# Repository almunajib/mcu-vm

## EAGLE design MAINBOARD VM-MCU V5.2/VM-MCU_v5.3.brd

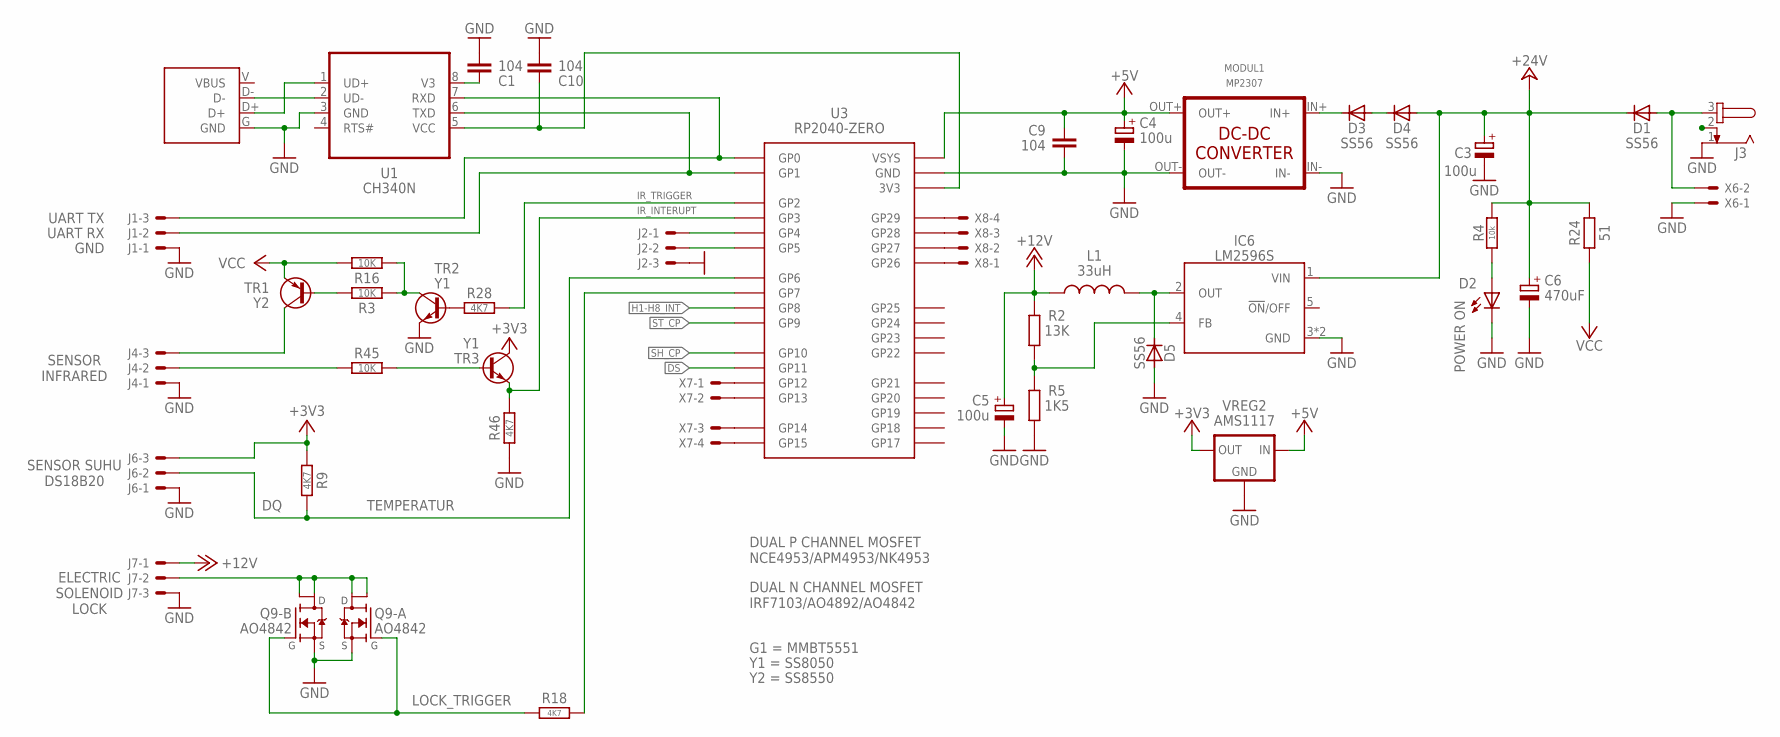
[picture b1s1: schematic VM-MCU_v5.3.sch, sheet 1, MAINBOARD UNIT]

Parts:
C1, C9, C10: 104; C1206
C3, C4, C5: 100u; UD-6,3X7,7_NICHICON
C6: 470uF; E5-10,5
D1, D3, D4, D5: SS56; DO214AC
D2: POWER ON; LED2835
IC6: LM2596S; TO263-5
J1, J6, J7: SOKET-3P_KF2510-2.54; KF2510-3P
J2: SOKET-3P_JST-XH-2.54; 3P-JST-XH
J3: JACK-DC_5.5X2.1MM; DC-5.5X2.1
J4: SOKET-3P_MOLEX-3.96; 3P-MOLEX
L1: 33uH; CDRH104
MODUL1: MP2307
Q9: AO4842; SO-8
R2: 13K; R1206
R3, R16, R45: 10K; R1206
R4: 10k; R1206
R5: 1K5; R1206
R9, R18, R28, R46: 4K7; R1206
R24: 51; R2512
TR1: Y2; SOT23-BEC
TR2, TR3: Y1; SOT23-BEC
U1: CH340N; SO-8
U3: RP2040-ZERO; PICO-ZERO
U$3: USB-C_BREAKOUT_; USB-C_4P
VREG2: AMS1117; SOT223
X6: SOKET-2P_MOLEX-3.96; 2P-MOLEX
X7, X8: SOKET-4P_JST-XH-2.54; 4P-JST-XH

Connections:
+3V3: J6.3, R9.1, TR3.C, VREG2.4 (OUT); also elsewhere on the board
+5V: C4.+, C9.1, MODUL1.OUT+, U3.5V (VSYS), VREG2.3 (IN); also elsewhere on the board
+12V: C5.+, J7.1, L1.1, R2.1
+24V: C3.+, C6.+, D1.C, D4.A, IC6.1 (VIN), R4.2, R24.2; also elsewhere on the board
DS: U3.P11 (GP11); also elsewhere on the board
GND: C1.2, C3.-, C4.-, C5.-, C6.-, C9.2, C10.2, D2.C, D5.A, IC6.3 (GND), IC6.6 (GND), J1.1, J2.3, J3.1, J4.1, J6.1, J7.3, MODUL1.IN-, MODUL1.OUT-, Q9.1 (S), Q9.3 (S), R5.2, R46.1, TR2.E, U1.3 (GND), U3.G (GND), U$3.G (GND), VREG2.1 (GND), X6.1; also elsewhere on the board
H1-H8_INT: U3.P8 (GP8); also elsewhere on the board
unnamed: J1.3, U1.7 (RXD), U3.P0 (GP0)
unnamed: J1.2, U1.6 (TXD), U3.P1 (GP1)
unnamed: D1.A, J3.3, X6.2
unnamed: D2.A, R4.1
unnamed: J2.1, U3.P4 (GP4)
unnamed: R3.2, R16.2, TR2.C
unnamed: R3.1, TR1.B
unnamed: J2.2, U3.P5 (GP5)
unnamed: C10.1, U1.5 (VCC), U3.3V3
unnamed: J4.3, TR1.C
unnamed: Q9.2 (G), Q9.4 (G), R18.2
unnamed: C1.1, U1.8 (V3)
unnamed: U1.2 (UD-), U$3.D-
unnamed: U1.1 (UD+), U$3.D+
unnamed: J7.2, Q9.5 (D1), Q9.6 (D2), Q9.7 (D2), Q9.8 (D1)
unnamed: D3.C, MODUL1.IN+
unnamed: D3.A, D4.C
unnamed: U3.P12 (GP12), X7.1
unnamed: U3.P13 (GP13), X7.2
unnamed: U3.P14 (GP14), X7.3
unnamed: U3.P15 (GP15), X7.4
unnamed: D5.C, IC6.2 (OUT), L1.2
unnamed: U3.P26 (GP26), X8.1
unnamed: U3.P27 (GP27), X8.2
unnamed: IC6.4 (FB), R2.2, R5.1
unnamed: U3.P28 (GP28), X8.3
unnamed: R28.1, TR2.B
unnamed: R45.1, TR3.B
unnamed: U3.P29 (GP29), X8.4
unnamed: J4.2, R45.2
P2: R28.2, U3.P2 (GP2)
P3: R46.2, TR3.E, U3.P3 (GP3)
P6: J6.2, R9.2, U3.P6 (GP6)
P7: R18.1, U3.P7 (GP7)
SH_CP: U3.P10 (GP10); also elsewhere on the board
ST_CP: U3.P9 (GP9); also elsewhere on the board
VCC: R16.1, R24.1, TR1.E

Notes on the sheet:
UART RX
UART TX
SENSOR SUHU DS18B20
SENSOR INFRARED
ELECTRIC SOLENOID LOCK
IR_TRIGGER
TEMPERATUR
IR_INTERUPT
DUAL P CHANNEL MOSFET NCE4953/APM4953/NK4953
DUAL N CHANNEL MOSFET IRF7103/AO4892/AO4842
LOCK_TRIGGER
G1 = MMBT5551
GND
Y1 = SS8050
Y2 = SS8550

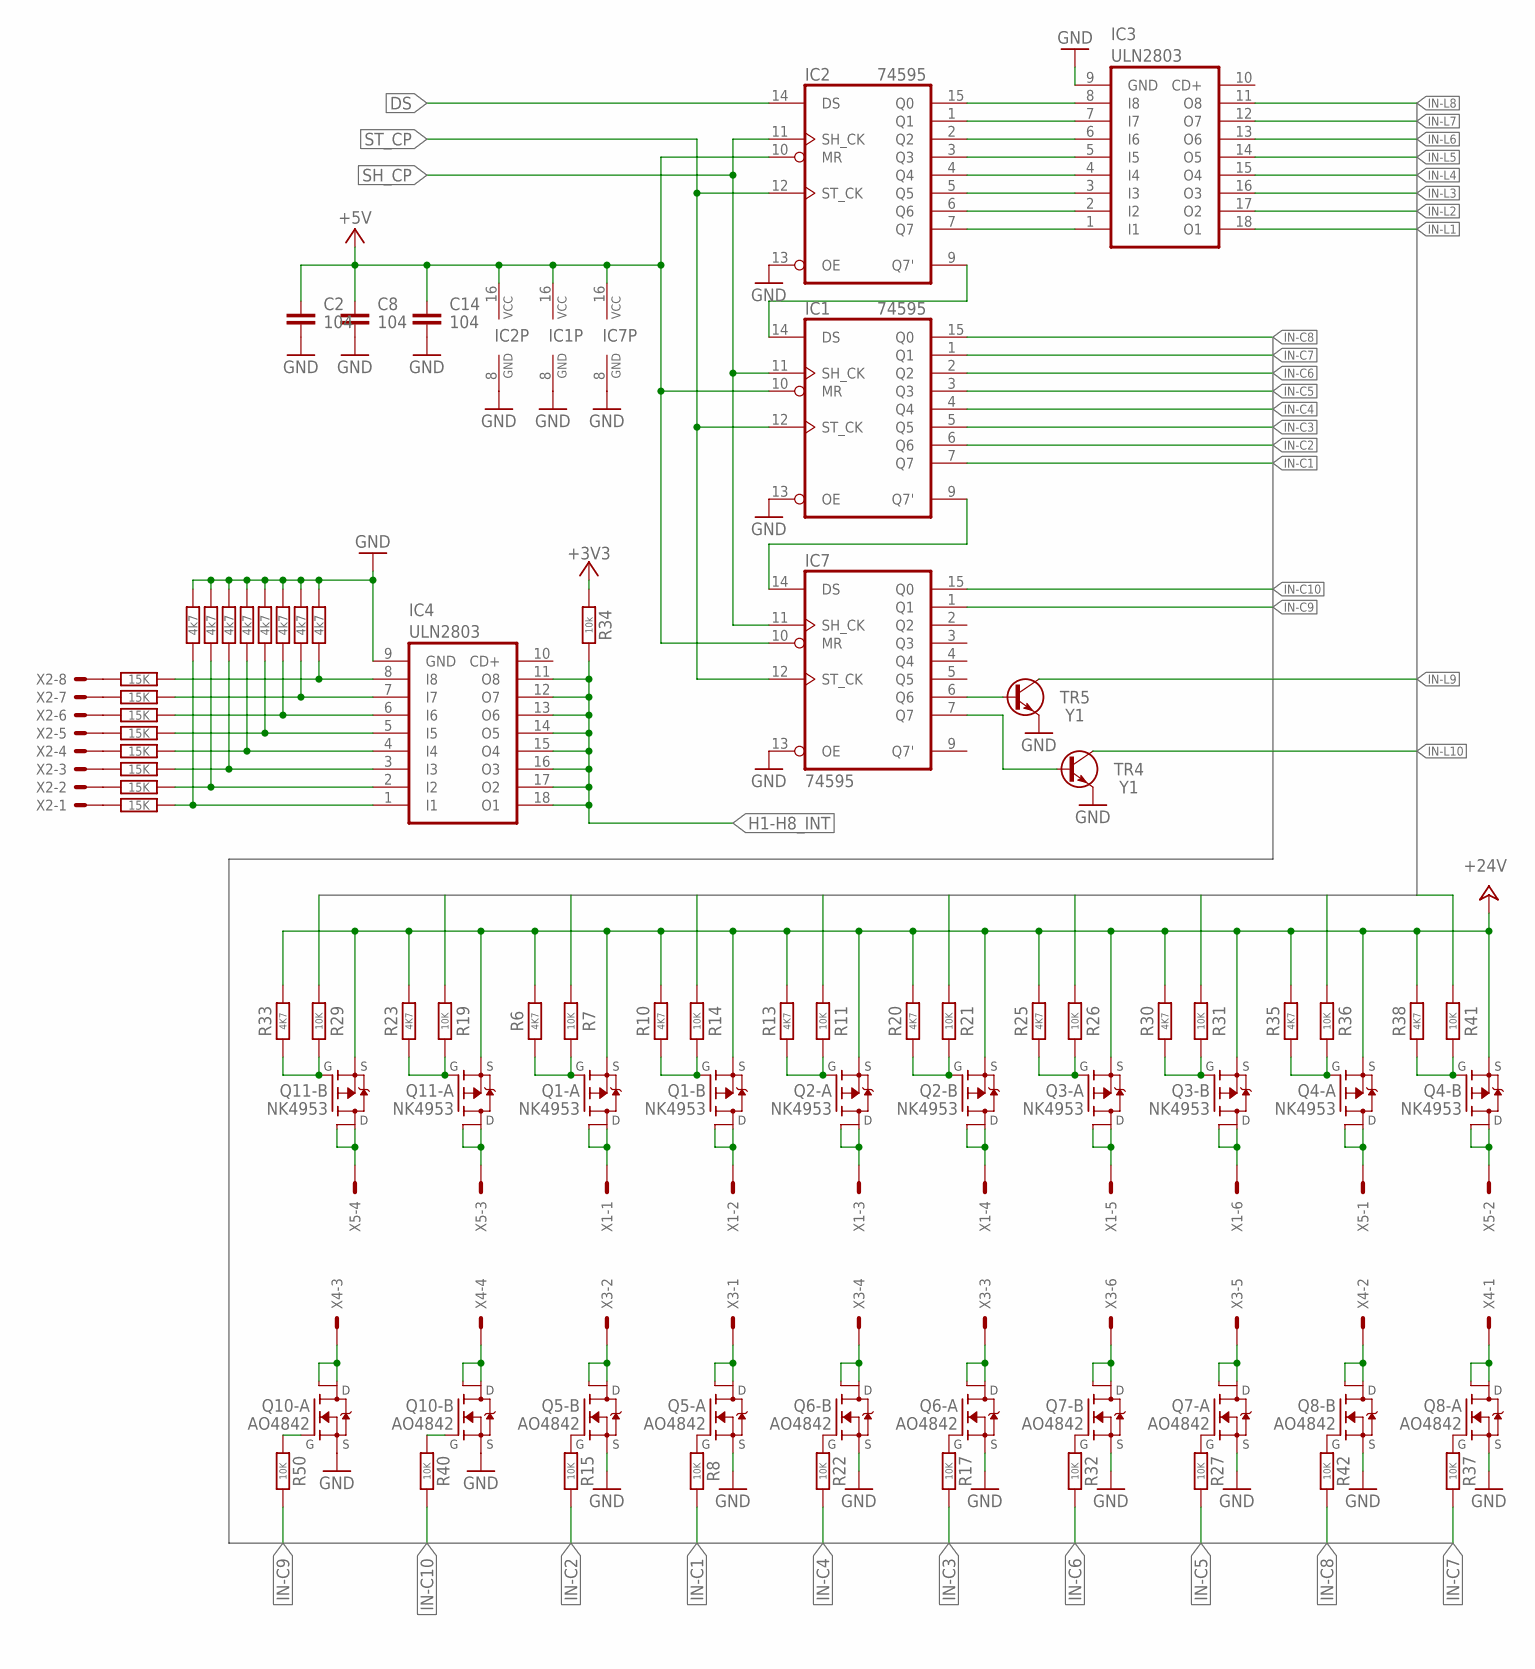
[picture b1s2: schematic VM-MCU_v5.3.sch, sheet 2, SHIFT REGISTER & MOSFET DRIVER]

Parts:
C2, C8, C14: 104; C1206
IC1, IC2, IC7: 74595; SO16
IC3, IC4: ULN2803; SO18W
Q1, Q2, Q3, Q4, Q11: NK4953; SO-8
Q5, Q6, Q7, Q8, Q10: AO4842; SO-8
R1, R12, R39, R43, R44, R47, R48, R49: 15K; R0805
R6, R10, R13, R20, R23, R25, R30, R33, R35, R38: 4K7; R1206
R7, R8, R11, R14, R15, R17, R19, R21, R22, R26, R27, R29, R31, R32, R36, R37, R40, R41, R42, R50: 10K; R1206
R34: 10k; R1206
R51, R52, R53, R54, R55, R56, R57, R58: 4k7; R0805
TR4, TR5: Y1; SOT23-BEC
X1, X3: SOKET-6P_MOLEX-3.96; 6P-MOLEX
X2: SOKET-8P_MOLEX-3.96; 8P-MOLEX
X4, X5: SOKET-4P_MOLEX-3.96; 4P-MOLEX

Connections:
+3V3: R34.2; also elsewhere on the board
+5V: C2.1, C8.1, C14.1, IC1.10 (MR), IC1.16 (VCC), IC2.10 (MR), IC2.16 (VCC), IC7.10 (MR), IC7.16 (VCC); also elsewhere on the board
+24V: Q1.1 (S), Q1.3 (S), Q2.1 (S), Q2.3 (S), Q3.1 (S), Q3.3 (S), Q4.1 (S), Q4.3 (S), Q11.1 (S), Q11.3 (S), R6.1, R10.1, R13.1, R20.1, R23.1, R25.1, R30.1, R33.1, R35.1, R38.1; also elsewhere on the board
C1: Q5.5 (D1), Q5.6 (D2), X3.2
C2: Q5.7 (D2), Q5.8 (D1), X3.1
C3: Q6.5 (D1), Q6.6 (D2), X3.4
C4: Q6.7 (D2), Q6.8 (D1), X3.3
C5: Q7.5 (D1), Q7.6 (D2), X3.6
C6: Q7.7 (D2), Q7.8 (D1), X3.5
C7: Q8.5 (D1), Q8.6 (D2), X4.2
C8: Q8.7 (D2), Q8.8 (D1), X4.1
DS: IC2.14 (DS); also elsewhere on the board
GND: C2.2, C8.2, C14.2, IC1.8 (GND), IC1.13 (OE), IC2.8 (GND), IC2.13 (OE), IC3.9 (GND), IC4.9 (GND), IC7.8 (GND), IC7.13 (OE), Q5.1 (S), Q5.3 (S), Q6.1 (S), Q6.3 (S), Q7.1 (S), Q7.3 (S), Q8.1 (S), Q8.3 (S), Q10.1 (S), Q10.3 (S), R51.1, R52.1, R53.1, R54.1, R55.1, R56.1, R57.1, R58.1, TR4.E, TR5.E; also elsewhere on the board
H1-H8_INT: IC4.11 (O8), IC4.12 (O7), IC4.13 (O6), IC4.14 (O5), IC4.15 (O4), IC4.16 (O3), IC4.17 (O2), IC4.18 (O1), R34.1; also elsewhere on the board
I1: IC4.6 (I6), R39.1, R53.2
I2: IC4.5 (I5), R43.1, R54.2
I3: IC4.4 (I4), R44.1, R55.2
I4: IC4.3 (I3), R47.1, R56.2
I5: IC4.2 (I2), R48.1, R57.2
I6: IC4.1 (I1), R49.1, R58.2
IN-C1: IC1.7 (Q7), R8.2
IN-C2: IC1.6 (Q6), R15.2
IN-C3: IC1.5 (Q5), R17.2
IN-C4: IC1.4 (Q4), R22.2
IN-C5: IC1.3 (Q3), R27.2
IN-C6: IC1.2 (Q2), R32.2
IN-C7: IC1.1 (Q1), R37.2
IN-C8: IC1.15 (Q0), R42.2
IN-C9: IC7.1 (Q1), R50.2
IN-C10: IC7.15 (Q0), R40.2
IN-L1: IC3.18 (O1), R7.2
IN-L2: IC3.17 (O2), R14.2
IN-L3: IC3.16 (O3), R11.2
IN-L4: IC3.15 (O4), R21.2
IN-L5: IC3.14 (O5), R26.2
IN-L6: IC3.13 (O6), R31.2
IN-L7: IC3.12 (O7), R36.2
IN-L8: IC3.11 (O8), R41.2
IN-L9: R19.2, TR5.C
IN-L10: R29.2, TR4.C
L1: Q1.7 (D2), Q1.8 (D1), X1.1
L2: Q1.5 (D1), Q1.6 (D2), X1.2
L3: Q2.7 (D2), Q2.8 (D1), X1.3
L4: Q2.5 (D1), Q2.6 (D2), X1.4
L5: Q3.7 (D2), Q3.8 (D1), X1.5
L6: Q3.5 (D1), Q3.6 (D2), X1.6
L7: Q4.7 (D2), Q4.8 (D1), X5.1
L8: Q4.5 (D1), Q4.6 (D2), X5.2
unnamed: IC4.8 (I8), R12.1, R51.2
unnamed: IC4.7 (I7), R1.1, R52.2
unnamed: IC2.15 (Q0), IC3.8 (I8)
unnamed: R43.2, X2.5
unnamed: R44.2, X2.4
unnamed: IC2.1 (Q1), IC3.7 (I7)
unnamed: Q1.2 (G), R6.2, R7.1
unnamed: R47.2, X2.3
unnamed: Q5.2 (G), R8.1
unnamed: Q5.4 (G), R15.1
unnamed: Q1.4 (G), R10.2, R14.1
unnamed: IC2.2 (Q2), IC3.6 (I6)
unnamed: Q2.2 (G), R11.1, R13.2
unnamed: R39.2, X2.6
unnamed: R48.2, X2.2
unnamed: IC2.3 (Q3), IC3.5 (I5)
unnamed: Q6.2 (G), R17.1
unnamed: R1.2, X2.7
unnamed: IC2.4 (Q4), IC3.4 (I4)
unnamed: R49.2, X2.1
unnamed: Q6.4 (G), R22.1
unnamed: Q2.4 (G), R20.2, R21.1
unnamed: Q7.2 (G), R27.1
unnamed: IC2.5 (Q5), IC3.3 (I3)
unnamed: IC2.6 (Q6), IC3.2 (I2)
unnamed: IC2.7 (Q7), IC3.1 (I1)
unnamed: Q7.4 (G), R32.1
unnamed: Q8.2 (G), R37.1
unnamed: Q3.2 (G), R25.2, R26.1
unnamed: Q8.4 (G), R42.1
unnamed: R12.2, X2.8
unnamed: IC1.9 (Q7'), IC7.14 (DS)
unnamed: Q10.4 (G), R40.1
unnamed: Q3.4 (G), R30.2, R31.1
unnamed: Q11.4 (G), R29.1, R33.2
unnamed: Q10.2 (G), R50.1
unnamed: Q11.2 (G), R19.1, R23.2
unnamed: IC7.7 (Q7), TR4.B
unnamed: IC7.6 (Q6), TR5.B
unnamed: Q11.7 (D2), Q11.8 (D1), X5.3
unnamed: Q4.2 (G), R35.2, R36.1
unnamed: Q11.5 (D1), Q11.6 (D2), X5.4
unnamed: Q10.7 (D2), Q10.8 (D1), X4.3
unnamed: Q10.5 (D1), Q10.6 (D2), X4.4
unnamed: Q4.4 (G), R38.2, R41.1
unnamed: IC1.14 (DS), IC2.9 (Q7')
SH_CP: IC1.11 (SH_CK), IC2.11 (SH_CK), IC7.11 (SH_CK); also elsewhere on the board
ST_CP: IC1.12 (ST_CK), IC2.12 (ST_CK), IC7.12 (ST_CK); also elsewhere on the board

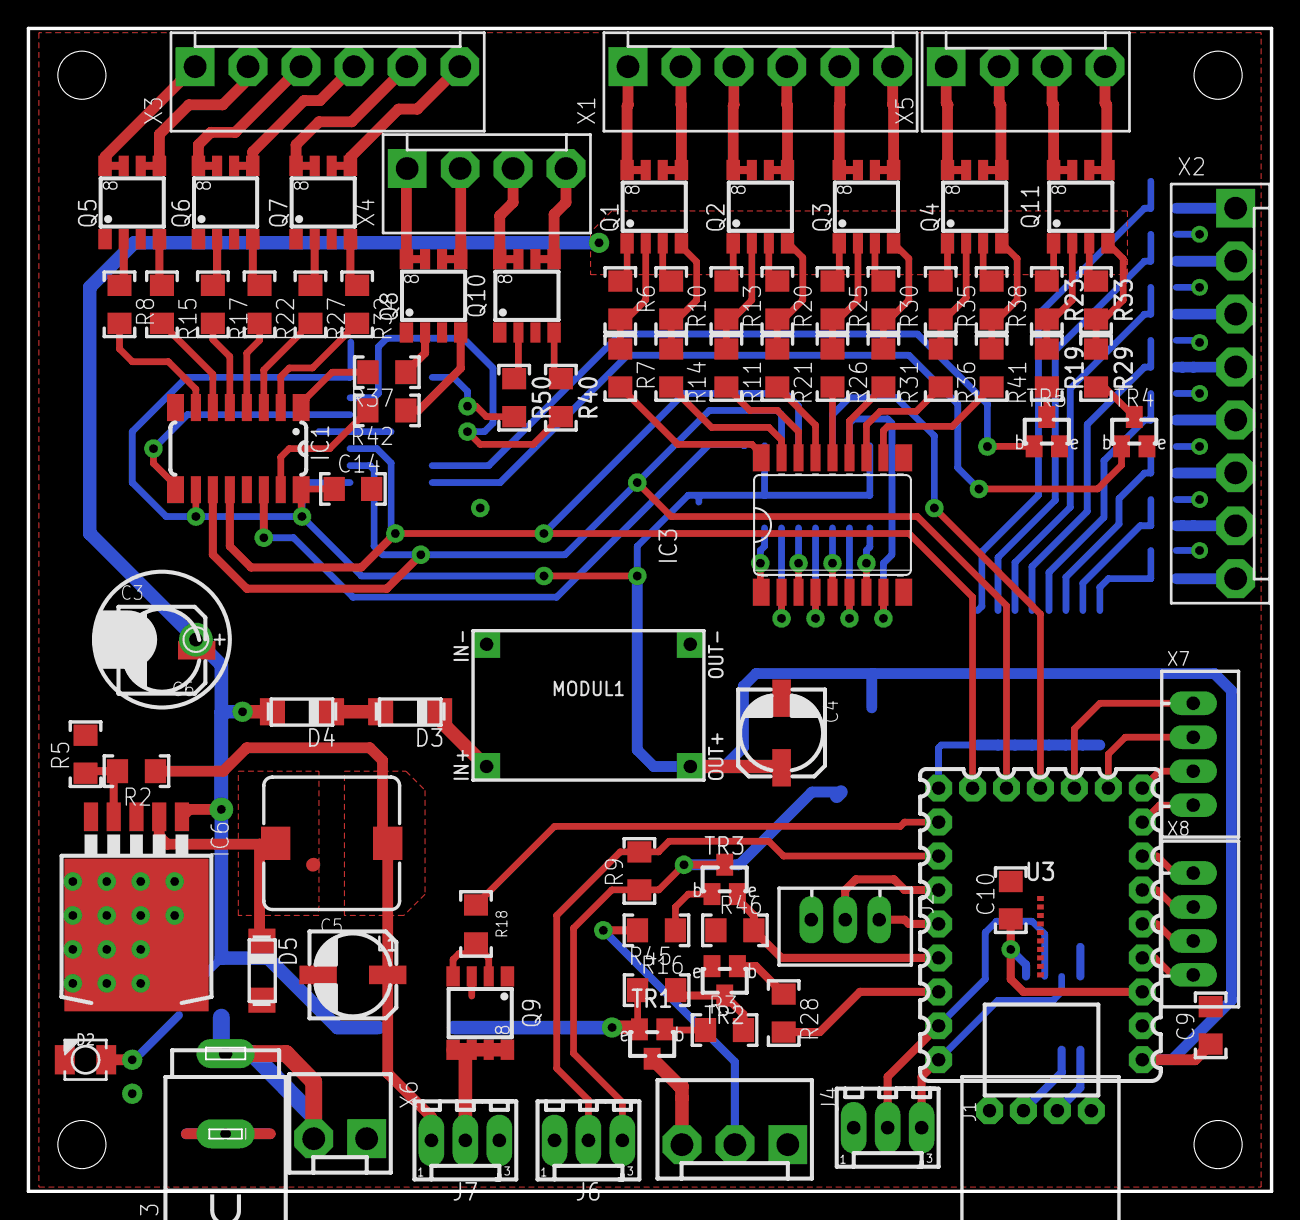
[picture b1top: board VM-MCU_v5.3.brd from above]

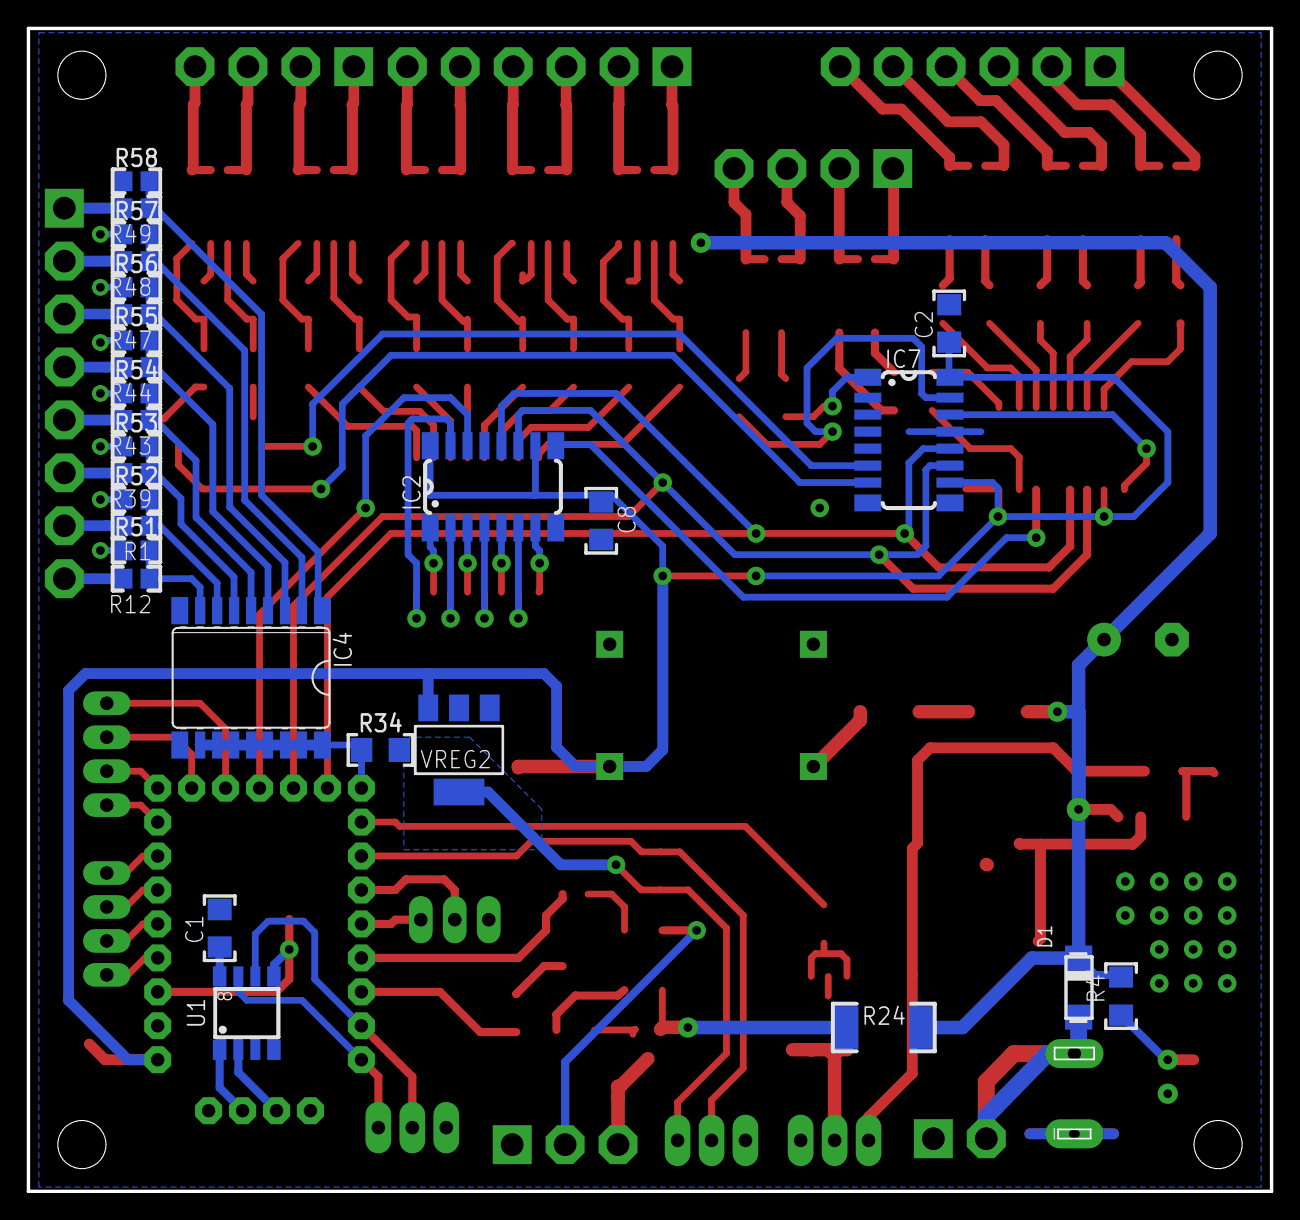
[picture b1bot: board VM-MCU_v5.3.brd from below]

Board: 2 copper layers, 93.0 x 87.0 mm, 116 parts (28 on the bottom side), 132 nets.

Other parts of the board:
U$1: BOX-PLC_115X90_V2

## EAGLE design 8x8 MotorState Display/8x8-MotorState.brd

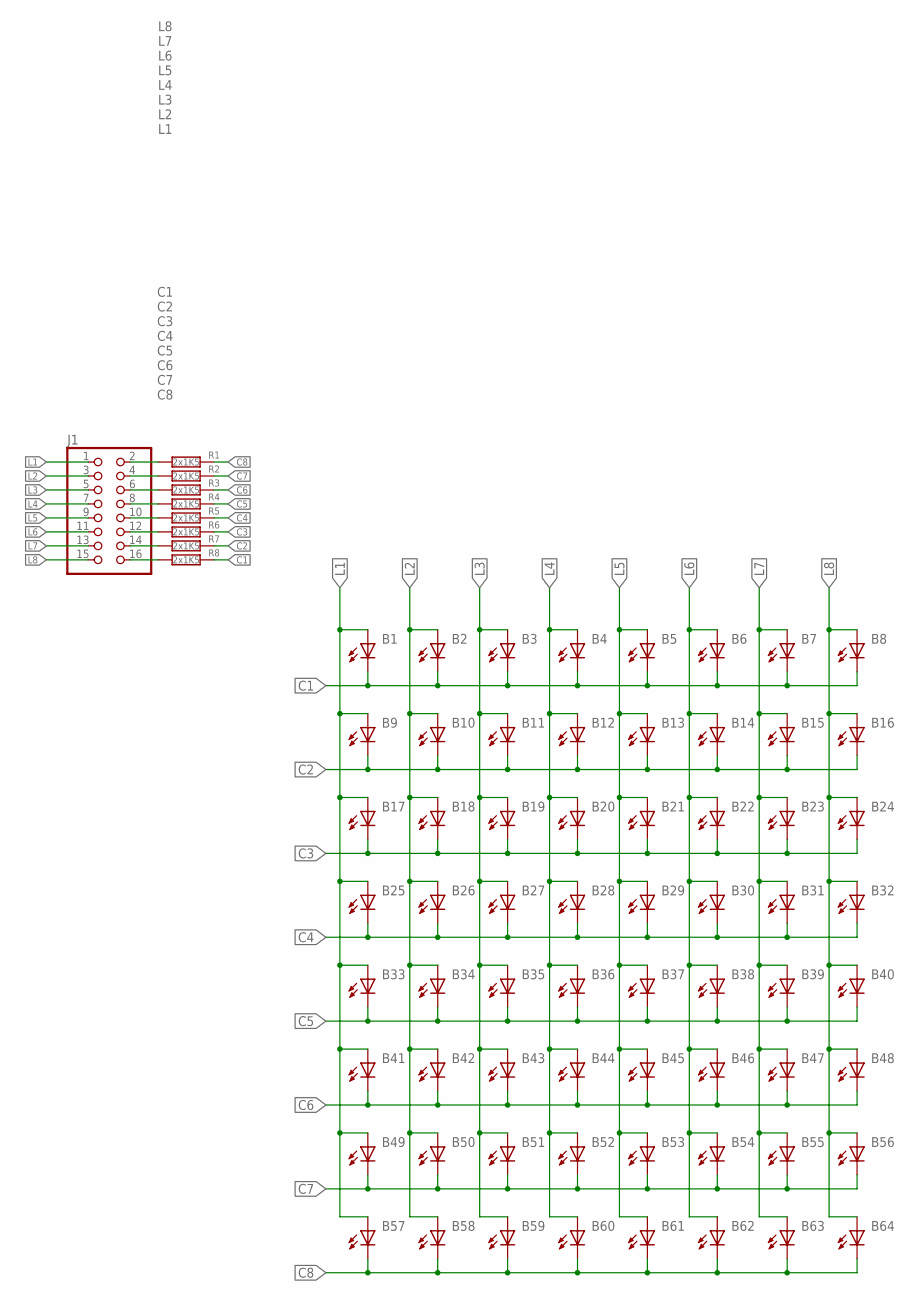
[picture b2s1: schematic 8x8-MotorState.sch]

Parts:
B1, B2, B3, B4, B5, B6, B7, B8, B9, B10, B11, B12, B13, B14, B15, B16, B17, B18, B19, B20, B21, B22, B23, B24, B25, B26, B27, B28, B29, B30, B31, B32, B33, B34, B35, B36, B37, B38, B39, B40, B41, B42, B43, B44, B45, B46, B47, B48, B49, B50, B51, B52, B53, B54, B55, B56, B57, B58, B59, B60, B61, B62, B63, B64: LED2835
J1: PINHEAD_2X8PTH; PINHEAD-2X08
R1, R2, R3, R4, R5, R6, R7, R8: 2x1K5; R1206

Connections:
C1: B1.C, B2.C, B3.C, B4.C, B5.C, B6.C, B7.C, B8.C, R8.1
C2: B9.C, B10.C, B11.C, B12.C, B13.C, B14.C, B15.C, B16.C, R7.1
C3: B17.C, B18.C, B19.C, B20.C, B21.C, B22.C, B23.C, B24.C, R6.1
C4: B25.C, B26.C, B27.C, B28.C, B29.C, B30.C, B31.C, B32.C, R5.1
C5: B33.C, B34.C, B35.C, B36.C, B37.C, B38.C, B39.C, B40.C, R4.1
C6: B41.C, B42.C, B43.C, B44.C, B45.C, B46.C, B47.C, B48.C, R3.1
C7: B49.C, B50.C, B51.C, B52.C, B53.C, B54.C, B55.C, B56.C, R2.1
C8: B57.C, B58.C, B59.C, B60.C, B61.C, B62.C, B63.C, B64.C, R1.1
L1: B1.A, B9.A, B17.A, B25.A, B33.A, B41.A, B49.A, B57.A, J1.1
L2: B2.A, B10.A, B18.A, B26.A, B34.A, B42.A, B50.A, B58.A, J1.3
L3: B3.A, B11.A, B19.A, B27.A, B35.A, B43.A, B51.A, B59.A, J1.5
L4: B4.A, B12.A, B20.A, B28.A, B36.A, B44.A, B52.A, B60.A, J1.7
L5: B5.A, B13.A, B21.A, B29.A, B37.A, B45.A, B53.A, B61.A, J1.9
L6: B6.A, B14.A, B22.A, B30.A, B38.A, B46.A, B54.A, B62.A, J1.11
L7: B7.A, B15.A, B23.A, B31.A, B39.A, B47.A, B55.A, B63.A, J1.13
L8: B8.A, B16.A, B24.A, B32.A, B40.A, B48.A, B56.A, B64.A, J1.15
unnamed: J1.2, R1.2
unnamed: J1.4, R2.2
unnamed: J1.6, R3.2
unnamed: J1.8, R4.2
unnamed: J1.10, R5.2
unnamed: J1.12, R6.2
unnamed: J1.14, R7.2
unnamed: J1.16, R8.2

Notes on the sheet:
C1 C2 C3 C4 C5 C6 C7 C8
L8 L7 L6 L5 L4 L3 L2 L1

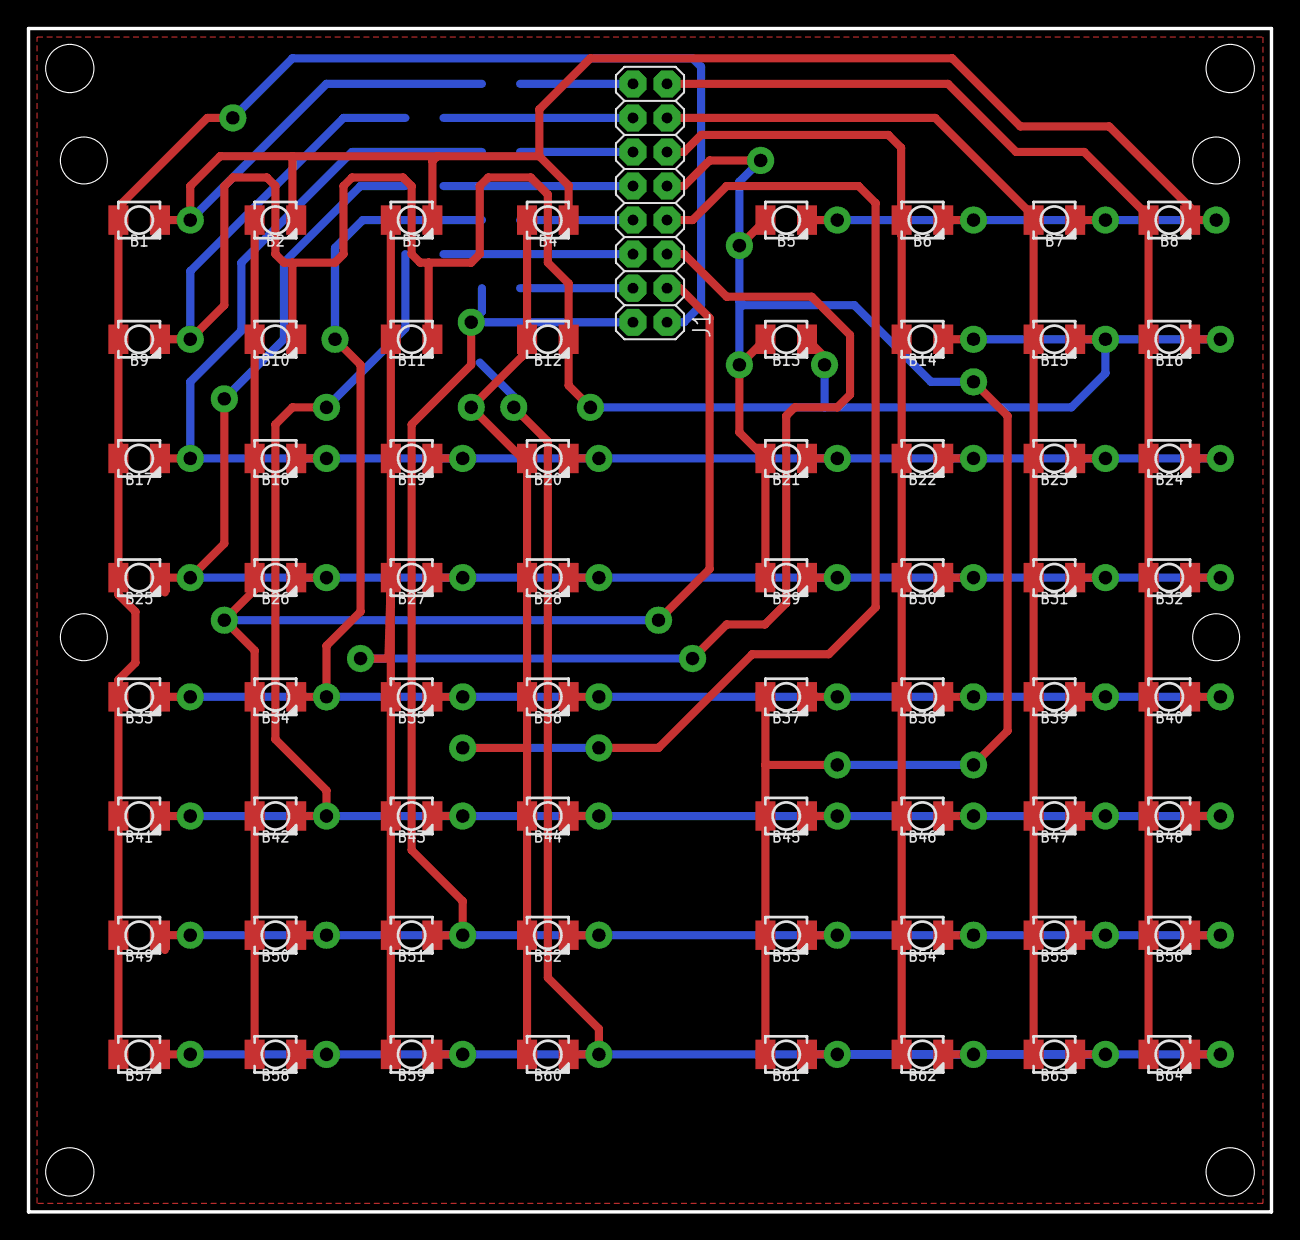
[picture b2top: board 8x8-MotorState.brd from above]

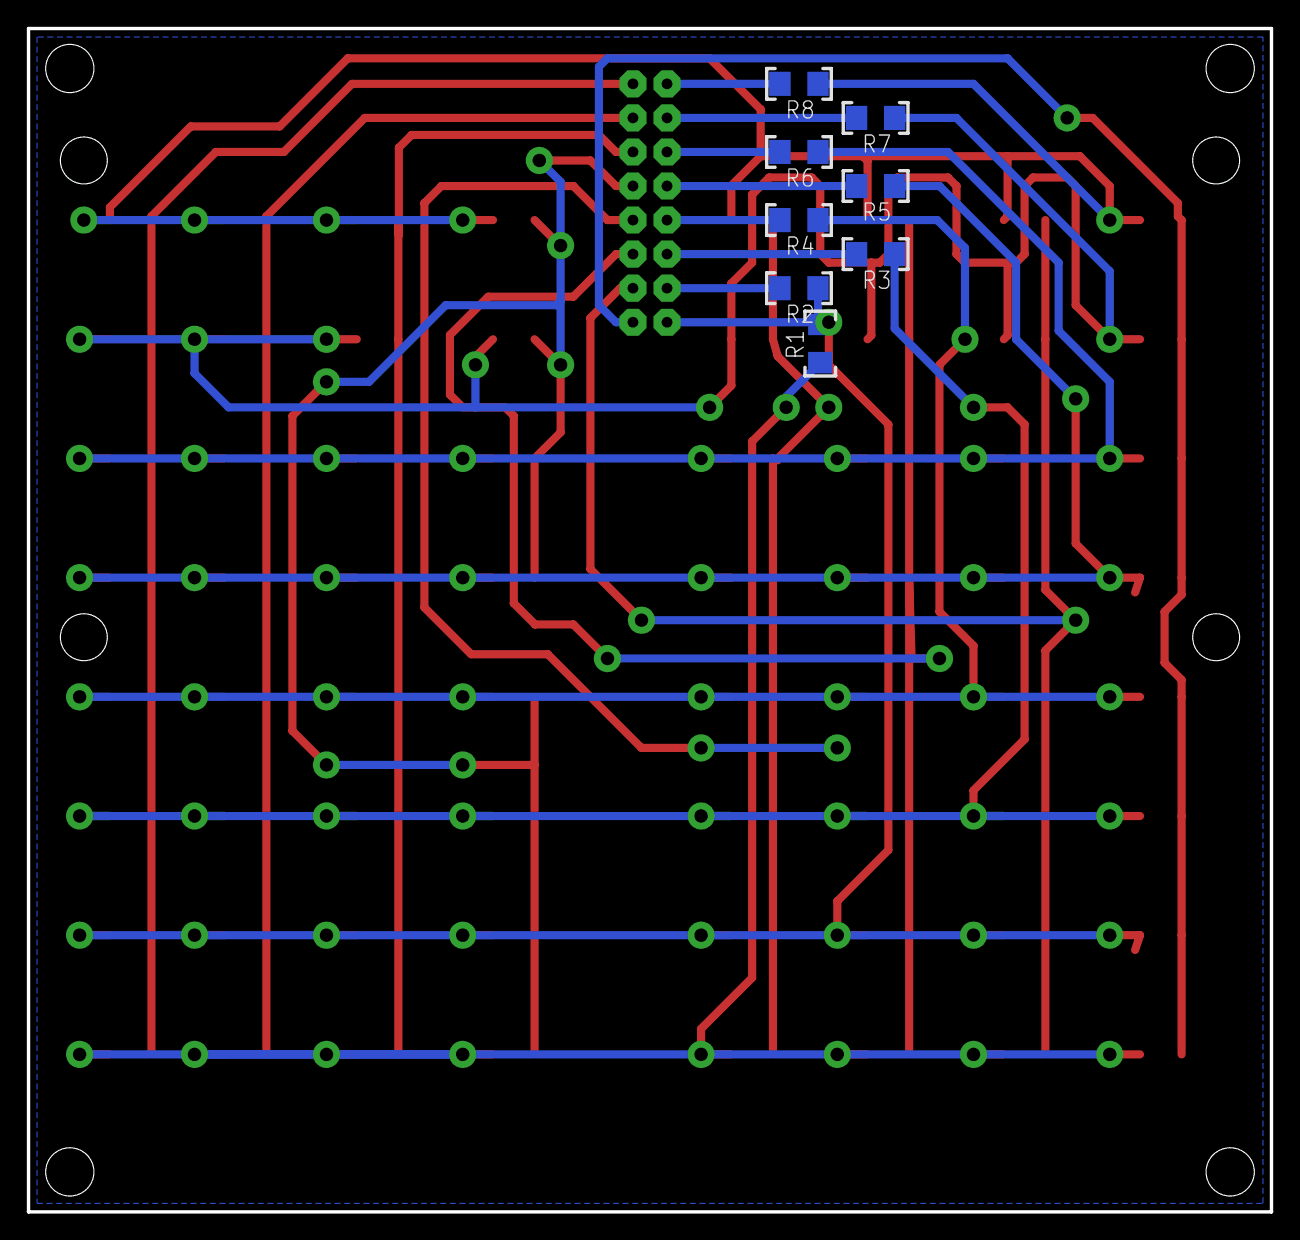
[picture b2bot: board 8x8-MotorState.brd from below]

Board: 2 copper layers, 92.7 x 88.3 mm, 74 parts (8 on the bottom side), 24 nets.

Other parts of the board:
U$1: BOX-PLC_115X90_V2

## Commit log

2025-02-11 mcu-vm_v4.5_tester
2025-02-11 file mainboard eagle
2025-02-11 Add files via upload
    main code for RPico2040 to control 8x8 Axis Motor
    Firmware for RPico2040 zero
2025-02-21 Tampilan Utama Serial Sender
    text di dalam kurung ( ) merupakan baris input perintah serial
    text di dalam tanda <> merupakan baris action dari mikrokontroller
    text di dalam tanda [ ] merupakan baris interupt yang mikrokontroller deteksi dari sensor IR ataupun trigger posisi dari limit switch pada Offset Motor
2025-03-06 Adding mainboard v4.6
2025-04-25 Update SerialSender_v2 dan main_RP2040-zero_v5.2 PCB untuk menambahkan perintah nyalakan motor dan autoset motor dengan konfigurasi 10 rak & 10 slot
2025-04-25 PENAMBAHAN desain MAINBOARD VM-MCU V5.2
